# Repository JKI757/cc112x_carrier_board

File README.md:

## About the Project

- This project is a simple PCB for a carrier board for a a Texas Instruments [CC112X EMK](https://www.ti.com/tool/CC1120EMK-420-470) development board and an STM32 Black Pill board, interface between the two, and jumper set to jump out the STM32 and attach an external microcontroller if necessary.

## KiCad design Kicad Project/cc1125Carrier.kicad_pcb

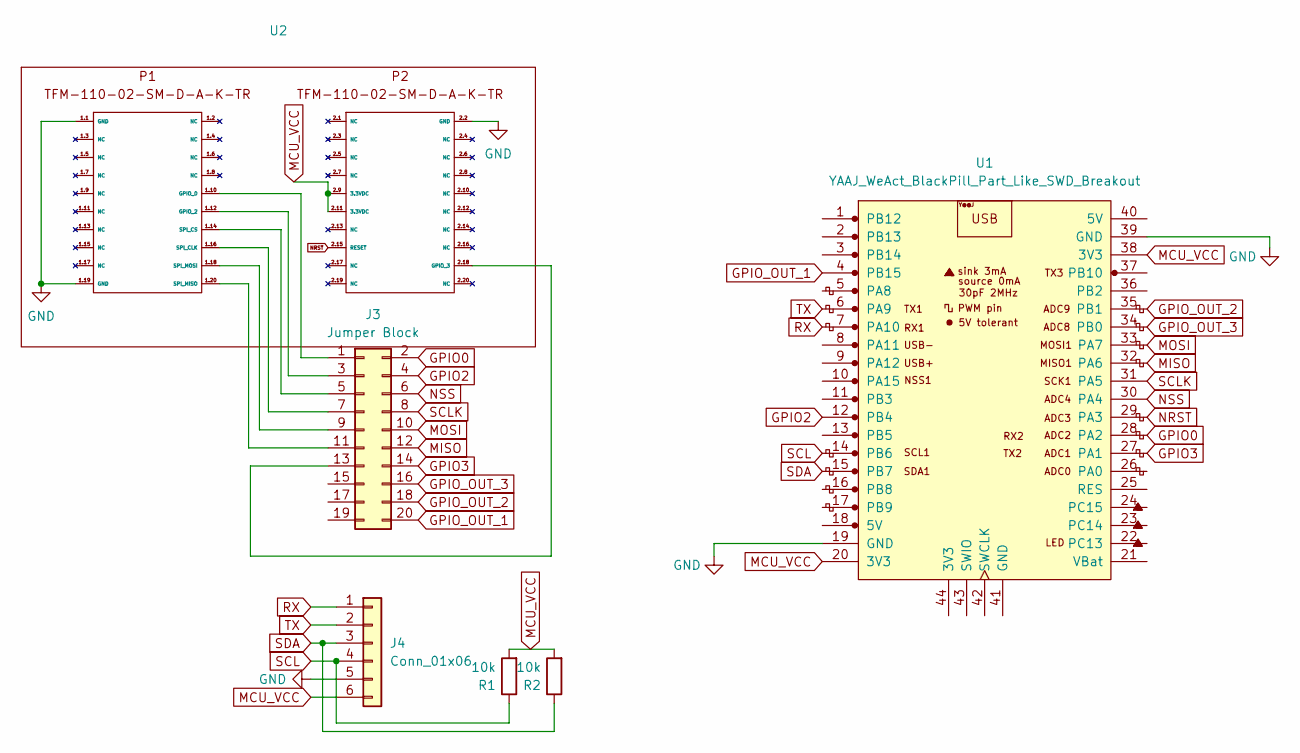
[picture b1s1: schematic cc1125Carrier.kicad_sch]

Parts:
J3: Jumper Block; PinHeader_2x10_P2.54mm_Vertical
J4: Conn_01x06; PinHeader_1x06_P2.54mm_Vertical
R1, R2: 10k; R_0402_1005Metric
U1: YAAJ_WeAct_BlackPill_Part_Like_SWD_Breakout; YAAJ_WeAct_BlackPill_SWD_2
U2: (no value)

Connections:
GND: J4.5, U1.19 (GND), U1.39 (GND), U2.1.1 (GND), U2.1.19 (GND), U2.2.2 (GND)
GPIO0: J3.2, U1.28 (PA2)
GPIO2: J3.4, U1.12 (PB4)
GPIO3: J3.14, U1.27 (PA1)
GPIO_OUT_1: J3.20, U1.4 (PB15)
GPIO_OUT_2: J3.18, U1.35 (PB1)
GPIO_OUT_3: J3.16, U1.34 (PB0)
MCU_VCC: J4.6, R1.2, R2.2, U1.20 (3V3), U1.38 (3V3), U2.2.9 (3.3VDC), U2.2.11 (3.3VDC)
MISO: J3.12, U1.32 (PA6)
MOSI: J3.10, U1.33 (PA7)
NRST: U1.29 (PA3), U2.2.15 (RESET)
NSS: J3.6, U1.30 (PA4)
unnamed: J3.1, U2.1.10 (GPIO_0)
unnamed: J3.3, U2.1.12 (GPIO_2)
unnamed: J3.5, U2.1.14 (SPI_CS)
unnamed: J3.7, U2.1.16 (SPI_CLK)
unnamed: J3.9, U2.1.18 (SPI_MOSI)
unnamed: J3.11, U2.1.20 (SPI_MISO)
unnamed: J3.13, U2.2.18 (GPIO_3)
RX: J4.1, U1.7 (PA10)
SCL: J4.4, R1.1, U1.14 (PB6)
SCLK: J3.8, U1.31 (PA5)
SDA: J4.3, R2.1, U1.15 (PB7)
TX: J4.2, U1.6 (PA9)

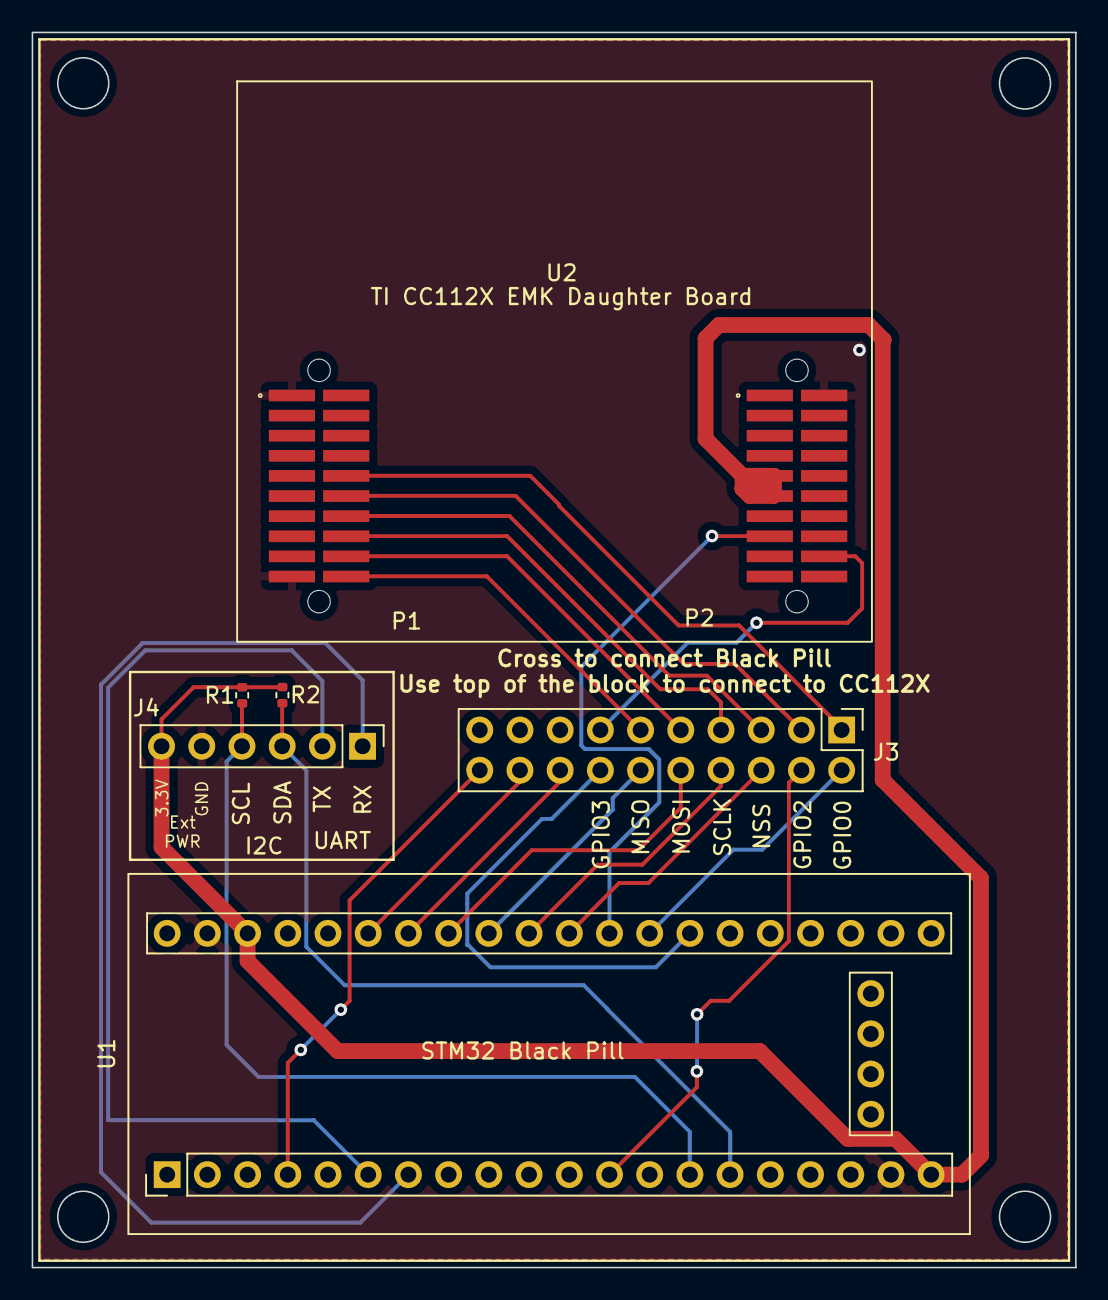
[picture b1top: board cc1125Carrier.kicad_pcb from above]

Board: 2 copper layers, 65.9 x 78.0 mm, 6 parts (0 on the bottom side), 24 nets.

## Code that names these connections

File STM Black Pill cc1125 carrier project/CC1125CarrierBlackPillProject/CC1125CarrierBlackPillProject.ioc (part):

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Mcu.Name=STM32F411C(C-E)Ux
Mcu.Package=UFQFPN48
Mcu.UserName=STM32F411CEUx
PA0-WKUP.GPIOParameters=GPIO_Label
PA0-WKUP.GPIO_Label=BOARD_KEY_SWITCH
PA0-WKUP.Signal=GPXTI0
PA1.GPIOParameters=GPIO_Label
PA1.GPIO_Label=TI_GPIO_3
PA1.Signal=GPXTI1
PA10.Mode=Asynchronous
PA10.Signal=USART1_RX
PA11.Mode=Device_Only
PA11.Signal=USB_OTG_FS_DM
PA12.Mode=Device_Only
PA12.Signal=USB_OTG_FS_DP
PA2.GPIOParameters=GPIO_Label
PA2.GPIO_Label=TI_GPIO_0
PA2.Signal=GPXTI2
PA3.GPIOParameters=GPIO_Label
PA3.GPIO_Label=TI_RESET
PA3.Signal=GPIO_Output
PA4.Mode=NSS_Signal_Hard_Output
PA4.Signal=SPI1_NSS
PA5.Mode=Full_Duplex_Master
PA5.Signal=SPI1_SCK
PA6.Mode=Full_Duplex_Master
PA6.Signal=SPI1_MISO
PA7.Mode=Full_Duplex_Master
PA7.Signal=SPI1_MOSI
PA9.Mode=Asynchronous
PA9.Signal=USART1_TX
PB0.GPIOParameters=GPIO_Label
PB0.GPIO_Label=GPIO_OUT_3
PB0.Signal=GPIO_Output
PB1.GPIOParameters=GPIO_Label
PB1.GPIO_Label=GPIO_OUT_2
PB1.Signal=GPIO_Output
PB15.GPIOParameters=GPIO_Label
PB15.GPIO_Label=GPIO_OUT_1
PB15.Signal=GPIO_Output
PB4.GPIOParameters=GPIO_Label
PB4.GPIO_Label=TI_GPIO_2
PB4.Signal=GPXTI4
PB6.Mode=I2C
PB6.Signal=I2C1_SCL
PB7.Mode=I2C
PB7.Signal=I2C1_SDA
PC13-ANTI_TAMP.GPIOParameters=GPIO_Label
PC13-ANTI_TAMP.GPIO_Label=BoardLED
PC13-ANTI_TAMP.Signal=GPIO_Output
PC14-OSC32_IN.Mode=LSE-External-Oscillator
PC14-OSC32_IN.Signal=RCC_OSC32_IN
PC15-OSC32_OUT.Mode=LSE-External-Oscillator
PC15-OSC32_OUT.Signal=RCC_OSC32_OUT
PH0\ -\ OSC_IN.Mode=HSE-External-Oscillator
PH0\ -\ OSC_IN.Signal=RCC_OSC_IN
PH1\ -\ OSC_OUT.Mode=HSE-External-Oscillator
PH1\ -\ OSC_OUT.Signal=RCC_OSC_OUT
RCC.HSE_VALUE=25000000
RCC.SYSCLKFreq_VALUE=16000000
board=custom

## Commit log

2022-05-14 first commit, passes all DRC
2022-05-14 update pullups on i2c, update images
2022-05-15 minor board tweaks
2022-05-15 fix images
2022-05-15 fix readme
2022-05-15 add STM project & re-arrange to include it
2022-05-15 move signals off of PA0 and PB2 due to conflict with stm32 buttons
2022-05-16 add STM32 Board LED & STM32 Board Key Switch
2022-05-20 tweak cc1125 footprint
2022-05-20 add emk daughter board symbol and footprint
